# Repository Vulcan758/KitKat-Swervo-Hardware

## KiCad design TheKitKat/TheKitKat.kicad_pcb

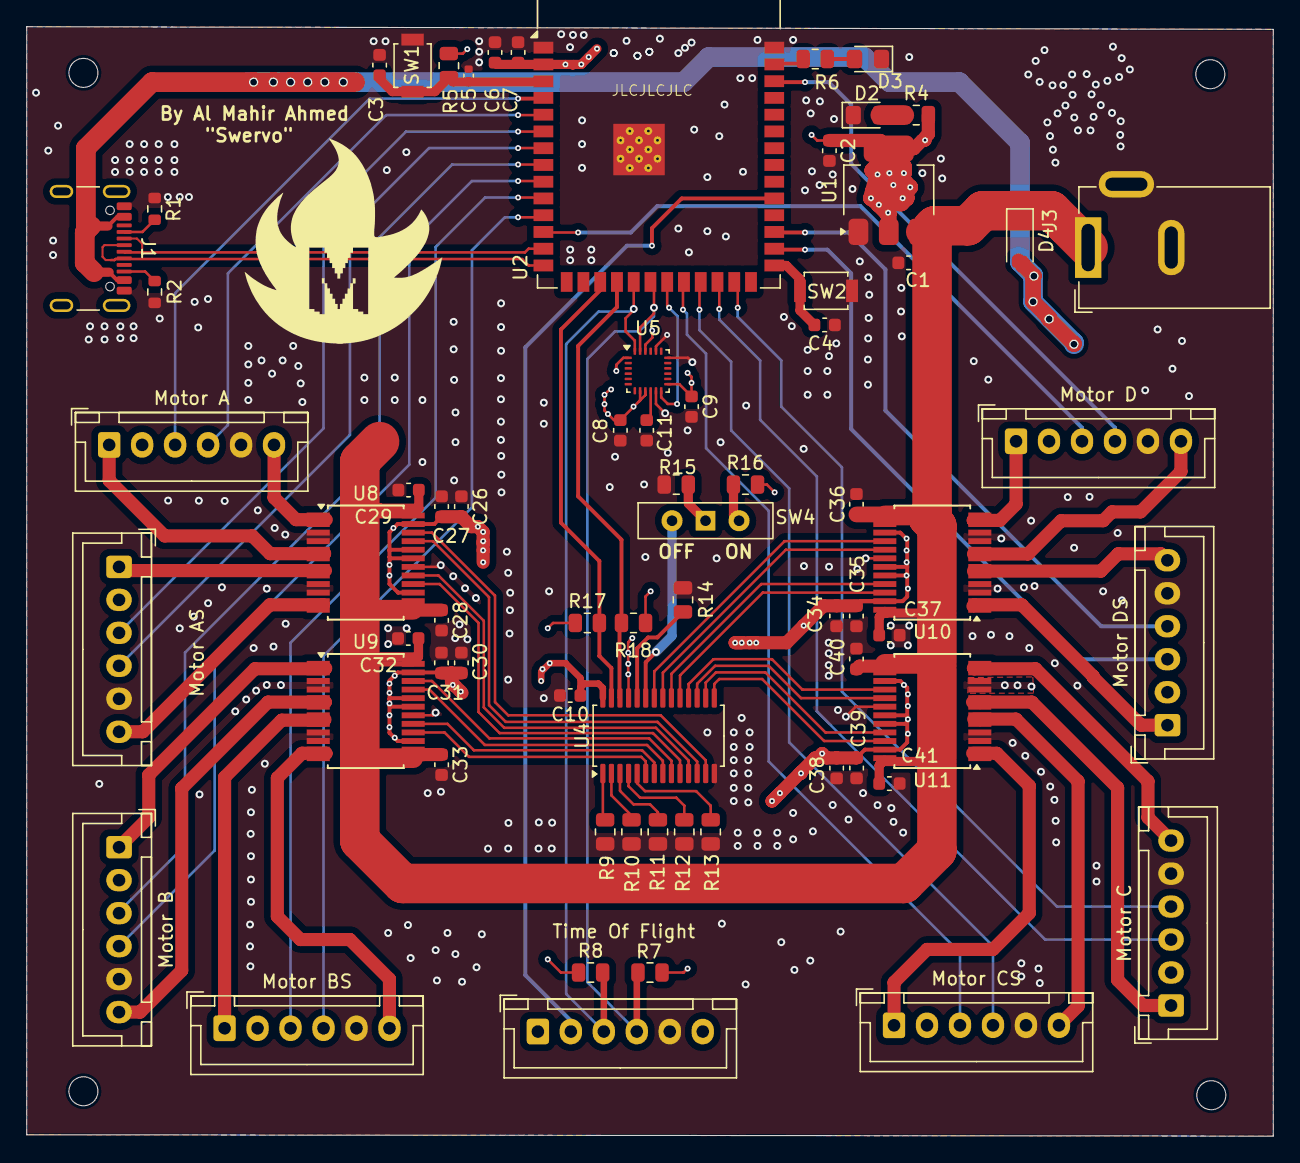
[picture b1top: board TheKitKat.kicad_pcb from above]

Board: 4 copper layers, 94.5 x 84.1 mm, 73 parts (0 on the bottom side), 77 nets.

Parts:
C1, C2: 22u; C_0603_1608Metric
C3, C4, C7, C9, C11: 0.1u; C_0603_1608Metric
C5: 1u; C_0402_1005Metric
C6, C10: 10u; C_0603_1608Metric
C8: 10n; C_0603_1608Metric
C26, C28, C30, C32, C34, C36, C38, C40: 0.1uF; C_0603_1608Metric
C27, C29, C31, C33, C35, C37, C39, C41: 10uF; C_0603_1608Metric
D2, D3: LED; LED_0805_2012Metric_Pad1.15x1.40mm_HandSolder
D4: 1N4148W; D_SOD-123
H1, H2, H3, H4: MountingHole; MountingHole_2.2mm_M2
J1: USB_C_Receptacle_USB2.0_16P; USB_C_Receptacle_GCT_USB4105-xx-A_16P_TopMnt_Horizontal
J3: Barrel_Jack_Switch; BarrelJack_GCT_DCJ200-10-A_Horizontal
Motor A: Motor B; JST_XH_B6B-XH-A_1x06_P2.50mm_Vertical
Motor AS: Motor B Swerve; JST_XH_B6B-XH-A_1x06_P2.50mm_Vertical
Motor B: Motor A; JST_XH_B6B-XH-A_1x06_P2.50mm_Vertical
Motor BS: Motor A Swerve; JST_XH_B6B-XH-A_1x06_P2.50mm_Vertical
Motor C: Motor D Swerve; JST_XH_B6B-XH-A_1x06_P2.50mm_Vertical
Motor CS: Motor D; JST_XH_B6B-XH-A_1x06_P2.50mm_Vertical
Motor D: Motor C Swerve; JST_XH_B6B-XH-A_1x06_P2.50mm_Vertical
Motor DS: Motor C; JST_XH_B6B-XH-A_1x06_P2.50mm_Vertical
R1, R2: 5.7k; R_0603_1608Metric
R4, R5, R6, R9, R10, R11, R12, R13, R14, R15, R16: 10k; R_0805_2012Metric
R7, R8: 4.9k; R_0805_2012Metric
R17, R18: 2.2k; R_0805_2012Metric
SW1, SW2: SW_Push; SW_SPST_B3U-1000P
SW4: MOTOR HARD SW; SW_Slide-03_Wuerth-WS-SLTV_10x2.5x6.4_P2.54mm
Time Of Flight: VL53L0X Breakout; JST_XH_B6B-XH-A_1x06_P2.50mm_Vertical
U1: AMS1117-3.3; SOT-223-3_TabPin2
U2: ESP32-S3-WROOM-1
U4: PCA9685PW; TSSOP-28_4.4x9.7mm_P0.65mm
U5: MPU-9250; InvenSense_QFN-24_3x3mm_P0.4mm
U8, U9, U10, U11: TB6612FNG; SSOP-24_5.3x8.2mm_P0.65mm

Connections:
+3.3V: C2.1, C6.1, C7.1, C8.1, C9.1, C10.1, C26.2, C27.2, C30.2, C31.2, C34.2, C35.2, C38.2, C39.2, Motor A.2, Motor AS.2, Motor B.2, Motor BS.2, Motor C.2, Motor CS.2, Motor D.2, Motor DS.2, R4.2, R5.1, R7.1, R8.1, R16.2, R17.1, R18.1, Time Of Flight.1, Time Of Flight.6, U1.2 (VO), U2.2 (3V3), U4.28 (VDD), U5.1 (RESV_VDDIO), U5.8 (VDDIO), U5.9 (AD0/MISO), U5.13 (VDD), U5.22 (~CS), U8.15 (PWMB), U8.19 (STBY), U8.20 (VCC), U8.23 (PWMA), U9.15 (PWMB), U9.19 (STBY), U9.20 (VCC), U9.23 (PWMA), U10.15 (PWMB), U10.19 (STBY), U10.20 (VCC), U10.23 (PWMA), U11.15 (PWMB), U11.19 (STBY), U11.20 (VCC), U11.23 (PWMA)
AIN_1: U4.8 (LED2), U9.21 (AIN1)
AIN_2: U4.9 (LED3), U9.22 (AIN2)
ASIN_1: U4.7 (LED1), U9.17 (BIN1)
ASIN_2: U4.6 (LED0), U9.16 (BIN2)
BIN_1: U4.12 (LED6), U8.21 (AIN1)
BIN_2: U4.13 (LED7), U8.22 (AIN2)
BSIN_1: U4.11 (LED5), U8.17 (BIN1)
BSIN_2: U4.10 (LED4), U8.16 (BIN2)
CIN_1: U4.20 (LED13), U10.21 (AIN1)
CIN_2: U4.19 (LED12), U10.22 (AIN2)
CSIN_1: U4.21 (LED14), U10.17 (BIN1)
CSIN_2: U4.22 (LED15), U10.16 (BIN2)
D+: J1.A6 (D+), J1.B6 (D+), U2.14 (IO20)
D-: J1.A7 (D-), J1.B7 (D-), U2.13 (IO19)
DIN_1: U4.16 (LED9), U11.21 (AIN1)
DIN_2: U4.15 (LED8), U11.22 (AIN2)
DSIN_1: U4.17 (LED10), U11.17 (BIN1)
DSIN_2: U4.18 (LED11), U11.16 (BIN2)
ENABLE: C3.1, C5.2, R5.2, SW1.2, U2.3 (EN)
ENCA1: Motor B.3, U2.8 (IO15)
ENCA2: Motor B.4, U2.9 (IO16)
ENCAS1: Motor BS.3, U2.10 (IO17)
ENCAS2: Motor BS.4, U2.11 (IO18)
ENCB1: Motor A.3, U2.4 (IO4)
ENCB2: Motor A.4, U2.5 (IO5)
ENCBS1: Motor AS.3, U2.6 (IO6)
ENCBS2: Motor AS.4, U2.7 (IO7)
ENCC1: Motor D.3, U2.12 (IO8)
ENCC2: Motor D.4, U2.38 (IO2)
ENCCS1: Motor DS.3, U2.28 (IO35)
ENCCS2: Motor DS.4, U2.29 (IO36)
ENCD1: Motor C.3, U2.24 (IO47)
ENCD2: Motor C.4, U2.25 (IO48)
ENCDS1: Motor CS.3, U2.22 (IO14)
ENCDS2: Motor CS.4, U2.23 (IO21)
GND: C1.2, C2.2, C3.2, C4.2, C5.1, C6.2, C7.2, C8.2, C9.2, C10.2, C11.1, C26.1, C27.1, C28.2, C29.2, C30.1, C31.1, C32.2, C33.2, C34.1, C35.1, C36.2, C37.2, C38.1, C39.1, C40.2, C41.2, D2.1 (K), D3.1 (K), J1.A1 (GND), J1.A12 (GND), J1.B1 (GND), J1.B12 (GND), J3.2, J3.3, Motor A.5, Motor AS.5, Motor B.5, Motor BS.5, Motor C.5, Motor CS.5, Motor D.5, Motor DS.5, R1.1, R2.1, R9.2, R10.2, R11.2, R12.2, R13.2, R14.2, R15.2, SW1.1, SW2.1, Time Of Flight.5, U1.1 (GND), U2.1 (GND), U2.40 (GND), U2.41 (GND), U4.14 (VSS), U4.25 (EXTCLK), U5.11 (FSYNC), U5.18 (GND), U5.20 (RESV_GND), U8.3 (PGND1), U8.4 (PGND1), U8.9 (PGND2), U8.10 (PGND2), U8.18 (GND), U9.3 (PGND1), U9.4 (PGND1), U9.9 (PGND2), U9.10 (PGND2), U9.18 (GND), U10.3 (PGND1), U10.4 (PGND1), U10.9 (PGND2), U10.10 (PGND2), U10.18 (GND), U11.3 (PGND1), U11.4 (PGND1), U11.9 (PGND2), U11.10 (PGND2), U11.18 (GND)
GPIO1_1: Time Of Flight.2, U2.31 (IO38)
INT: U2.21 (IO13), U5.12 (INT)
IO0: C4.1, SW2.2, U2.27 (IO0)
LED1: R6.2, U2.39 (IO1)
MA1: Motor B.1, U9.1 (AO1), U9.2 (AO1)
MA2: Motor B.6, U9.5 (AO2), U9.6 (AO2)
MAS1: Motor BS.6, U9.11 (BO1), U9.12 (BO1)
MAS2: Motor BS.1, U9.7 (BO2), U9.8 (BO2)
MB1: Motor A.6, U8.1 (AO1), U8.2 (AO1)
MB2: Motor A.1, U8.5 (AO2), U8.6 (AO2)
MBS1: Motor AS.6, U8.11 (BO1), U8.12 (BO1)
MBS2: Motor AS.1, U8.7 (BO2), U8.8 (BO2)
MC1: Motor DS.1, U10.1 (AO1), U10.2 (AO1)
MC2: Motor DS.6, U10.5 (AO2), U10.6 (AO2)
MCS1: Motor D.1, U10.11 (BO1), U10.12 (BO1)
MCS2: Motor D.6, U10.7 (BO2), U10.8 (BO2)
MD1: Motor CS.1, U11.1 (AO1), U11.2 (AO1)
MD2: Motor CS.6, U11.5 (AO2), U11.6 (AO2)
MDS1: Motor C.6, U11.11 (BO1), U11.12 (BO1)
MDS2: Motor C.1, U11.7 (BO2), U11.8 (BO2)
unnamed: D2.2 (A), R4.1
unnamed: D3.2 (A), R6.1
unnamed: J1.A5 (CC1), R1.2
unnamed: J1.B5 (CC2), R2.2
unnamed: R15.1, SW4.1 (A)
unnamed: R16.1, SW4.3 (C)
unnamed: R9.1, U4.1 (A0)
unnamed: R10.1, U4.2 (A1)
unnamed: R11.1, U4.3 (A2)
unnamed: R12.1, U4.4 (A3)
unnamed: R13.1, U4.5 (A4)
unnamed: R14.1, U4.24 (A5)
unnamed: C11.2, U5.10 (REGOUT)
OD: SW4.2 (B), U4.23 (~OE)
SCL0: R7.2, Time Of Flight.4, U2.20 (IO12), U5.23 (SCL/SCLK)
SCL1: R18.2, U2.18 (IO10), U4.26 (SCL)
SDA0: R8.2, Time Of Flight.3, U2.19 (IO11), U5.24 (SDA/MOSI)
SDA1: R17.2, U2.17 (IO9), U4.27 (SDA)
VBUS: D4.2 (A), J1.A4 (VBUS), J1.A9 (VBUS), J1.B4 (VBUS), J1.B9 (VBUS)
V_STABLE: C1.1, C28.1, C29.1, C32.1, C33.1, C36.1, C37.1, C40.1, C41.1, D4.1 (K), J3.1, U1.3 (VI), U8.13 (VM2), U8.14 (VM3), U8.24 (VM1), U9.13 (VM2), U9.14 (VM3), U9.24 (VM1), U10.13 (VM2), U10.14 (VM3), U10.24 (VM1), U11.13 (VM2), U11.14 (VM3), U11.24 (VM1)

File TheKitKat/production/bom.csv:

Designator,Footprint,Quantity,Value,LCSC Part #
"C1, C2",0603,2,22u,
"C10, C6",0603,2,10u,
"C11, C3, C4, C7, C9",0603,5,0.1u,
"C26, C28, C30, C32, C34, C36, C38, C40",0603,8,0.1uF,
"C27, C29, C31, C33, C35, C37, C39, C41",0603,8,10uF,
C5,0402,1,1u,
C8,0603,1,10n,
"D2, D3",0805,2,LED,
D4,D_SOD-123,1,1N4148W,
J1,USB_C_Receptacle_GCT_USB4105-xx-A_16P_TopMnt_Horizontal,1,USB_C_Receptacle_USB2.0_16P,
J3,BarrelJack_GCT_DCJ200-10-A_Horizontal,1,Barrel_Jack_Switch,
Motor A,JST_XH_B6B-XH-A_1x06_P2.50mm_Vertical,1,Motor B,
Motor AS,JST_XH_B6B-XH-A_1x06_P2.50mm_Vertical,1,Motor B Swerve,
Motor B,JST_XH_B6B-XH-A_1x06_P2.50mm_Vertical,1,Motor A,
Motor BS,JST_XH_B6B-XH-A_1x06_P2.50mm_Vertical,1,Motor A Swerve,
Motor C,JST_XH_B6B-XH-A_1x06_P2.50mm_Vertical,1,Motor D Swerve,
Motor CS,JST_XH_B6B-XH-A_1x06_P2.50mm_Vertical,1,Motor D,
Motor D,JST_XH_B6B-XH-A_1x06_P2.50mm_Vertical,1,Motor C Swerve,
Motor DS,JST_XH_B6B-XH-A_1x06_P2.50mm_Vertical,1,Motor C,
"R1, R2",0603,2,5.7k,
"R10, R11, R12, R13, R14, R15, R16, R4, R5, R6, R9",0805,11,10k,
"R17, R18",0805,2,2.2k,
"R7, R8",0805,2,4.9k,
"SW1, SW2",SW_SPST_B3U-1000P,2,SW_Push,
SW4,SW_Slide-03_Wuerth-WS-SLTV_10x2.5x6.4_P2.54mm,1,MOTOR HARD SW,
Time Of Flight,JST_XH_B6B-XH-A_1x06_P2.50mm_Vertical,1,VL53L0X Breakout,
U1,SOT-223-3_TabPin2,1,AMS1117-3.3,
"U10, U11, U8, U9",SSOP-24_5.3x8.2mm_P0.65mm,4,TB6612FNG,
U2,ESP32-S3-WROOM-1,1,ESP32-S3-WROOM-1,
U4,TSSOP-28_4.4x9.7mm_P0.65mm,1,PCA9685PW,
U5,InvenSense_QFN-24_3x3mm_P0.4mm,1,MPU-9250,
